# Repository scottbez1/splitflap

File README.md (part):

# Split-Flap Display

This is a DIY ESP32-based [split-flap display](https://en.wikipedia.org/wiki/Split-flap_display), optimized for easy assembly at home in small quantities but able to be scaled up to large affordable displays.

The [splitflap community Discord server](https://discord.com/invite/wgehm3PcrC) is the best place to keep up with the latest changes or ask questions about the project!

Want to help support development or just say "thanks"? Consider a one-time or monthly sponsorship:

| [:heart: Sponsor scottbez1 on GitHub](https://github.com/sponsors/scottbez1) |
|---|

**Using this project in a commercial setting or for paid client work?** Go right ahead - it's open source (just make sure to follow the terms of the Apache License)! I would, however, ask that you consider [sponsoring the project](https://github.com/sponsors/scottbez1). I've been developing and maintaining this project in my free time for over 10 years, and I'd love to continue working on it. Sponsorships allow me to pay for prototypes and development tools that make this project possible. Unlike pure software projects, every iteration has real hardware costs; sponsorships allow me to keep iterating and improving the project faster. Thank you!

# Current Status
[You can download the **latest stable releases** of the hardware designs from the official 'releases' page.](https://github.com/scottbez1/splitflap/releases)

Releases have been tested and used to produce working units, but as this is a continuously evolving open-source project, there may always be minor issues and/or incomplete documentation from time to time.

Here's a video of a large 108-module display powered by 18 Chainlink Driver boards and a Chainlink Base:

## Stable v2 Mechanical Release
As of 2025-01-19, the v2 refresh of the mechanical and sensor design is considered stable and recommended for new builds.

**Here's what's new in v2:**

- **52 flaps per module** for more character/symbol options
- **New printed flap design ("Epilogue")** with 52 flaps per set (see animation above), including several color-block flaps
- **Updated enclosure** and mechanical parts (laser-cut) to accomodate 52 flaps
  - Motor wires now exit downward for less awkward wiring!
- **New sensor PCB** that's easier to assemble and includes an LED for checking the magnet status
- **Software-configurable calibration** rather than mechanical sensor adjustment

**But many things are staying the same for easy upgrades/compatibility:**
- No change to flap dimensions!
- No changes to Chainlink Driver, Chainlink Buddy boards, or system architecture!
- 40-flap modules are still an officially supported option!
- Open source, as always!
- v0 parts (sensor kits) will continue to be stocked at Bezek Labs through mid-2025; don't worry if you haven't finished your build yet, the old sensor kits aren't going away for a little while!

I'd love to hear your thoughts and questions about this project, and happy to incorporate any feedback you might have into these designs! Please feel free (and encouraged) to [open GitHub issues](https://github.com/scottbez1/splitflap/issues/new), email me directly, reach out [on Bluesky](https://bsky.app/profile/scottbez1.bsky.social), and [get involved](https://github.com/scottbez1/splitflap/pulls) in the open source development and let's keep chatting and building together!

# Build Your Own
If you have any questions, please don't hesitate to ask in the [community Discord server](https://discord.gg/Hxnftc8PyW)!

* [**Documentation Index**](/docs/DocumentationIndex.md)
* [**Ordering guide (the "easy" route) v2**](/docs/v2/OrderingEasy.md)
* [**Comprehensive ordering guide**](/docs/v2/OrderingComplete.md)
* [**Chainlink Driver Electronics User Guide**](/docs/ElectronicsGuide.md)
* [**Assembly instructions v2**](/docs/v2/Assembly.md)
* [**Latest stable releases**](https://github.com/scottbez1/splitflap/releases)

# Table of Contents
- [Design Overview](#design-overview)
  - [Mechanical](#mechanical)
    - [Combined front panel (script)](#combined-front-panel-script)
    - [Flap font/sticker generator (script)](#flap-fontsticker-generator-script)
  - [Electronics](#electronics)
    - [Sensor PCBs](#sensor-pcbs-1-per-module)
    - [Chainlink Driver](#chainlink-driver-1-per-6-modules)
    - [Chainlink Buddy \[T-Display\]](#chainlink-buddy-t-display-1-for-entire-display)
    - [Advanced items](#advanced-items)
      - [Chainlink Buddy \[Breadboard\]](#chainlink-buddy-breadboard-1-for-entire-display-alternative-to-t-display)
      - [Chainlink Base](#chainlink-base-1-for-entire-display-large-displays)
    - [Older designs](#older-designs)
      - [Classic controller](#classic-controller-electronics-deprecated)
    + [Miscellaneous Tools](#miscellaneous-tools)
      - [3D Printed Tools](#3d-printed-tools)
      - [Chainlink Driver Tester](#chainlink-driver-tester)
  * [Code](#code)
    + [Firmware](#firmware)
    + [Computer Control Software](#computer-control-software)
- [Contributing/Modifying](#contributingmodifying)
  * [3D Design](#3d-design)
  * [Electronics Design](#electronics-design)

# Design Overview

## Mechanical
The mechanical/structural components are made from laser-cut 3mm MDF or acrylic, and held together with M4 bolts and nuts. The design is parametric and built using OpenSCAD. See below for more info on rendering/modifying the design.

You can view an interactive 3d model of the design [here](https://scottbez1.github.io/splitflap/embed.html?branch=master).

The v2 mechanical design officially supports variants with 52 flaps (perfect for use with the new ["Epilogue" printed flaps](https://bezeklabs.etsy.com/listing/1685633114/)) and 40 flaps. But you can always modify the design to customize it further.

### v2 (52-flap module option - recommended)

Instructions: [v2 assembly guide](/docs/v2/Assembly.md)

Module dimensions: 

Latest auto-generated (untested!) artifacts<sup>:warning:</sup>:
* For Ponoko 3mm MDF ([svg](https://s3.amazonaws.com/splitflap-artifacts/master/3d/3d_laser_vector-52-ponoko-3mm-mdf_1x.svg)) 
* For Ponoko 3mm acrylic ([svg](https://s3.amazonaws.com/splitflap-artifacts/master/3d/3d_laser_vector-52-ponoko-3mm-acrylic_1x.svg)) 
* For generic material (0.18mm kerf correction) ([svg](https://s3.amazonaws.com/splitflap-artifacts/master/3d/3d_laser_vector-52.svg))
* For Elecrow 3mm Wood ([zipped pdf](https://s3.amazonaws.com/splitflap-artifacts/master/3d/3d_laser_vector-52-elecrow-3mm-wood_1x.zip))
* For Elecrow 3mm Acrylic ([zipped pdf](https://s3.amazonaws.com/splitflap-artifacts/master/3d/3d_laser_vector-52-elecrow-3mm-acrylic_1x.zip))

<sup>:warning:</sup>For tested/stable/recommended artifacts, always use the [latest release](https://github.com/scottbez1/splitflap/releases) instead, as the links on this page will change over time.

### v2 (40-flap module option)

Instructions: [v2 assembly guide](/docs/v2/Assembly.md)

Module dimensions: 

Latest auto-generated (untested!) artifacts<sup>:warning:</sup>:
* For Ponoko 3mm MDF ([svg](https://s3.amazonaws.com/splitflap-artifacts/master/3d/3d_laser_vector-40-ponoko-3mm-mdf_1x.svg)) 
* For Ponoko 3mm acrylic ([svg](https://s3.amazonaws.com/splitflap-artifacts/master/3d/3d_laser_vector-40-ponoko-3mm-acrylic_1x.svg)) 
* For generic material (0.18mm kerf correction) ([svg](https://s3.amazonaws.com/splitflap-artifacts/master/3d/3d_laser_vector-52.svg))
* For Elecrow 3mm Wood ([zipped pdf](https://s3.amazonaws.com/splitflap-artifacts/master/3d/3d_laser_vector-40-elecrow-3mm-wood_1x.zip))
* For Elecrow 3mm Acrylic ([zipped pdf](https://s3.amazonaws.com/splitflap-artifacts/master/3d/3d_laser_vector-40-elecrow-3mm-acrylic_1x.zip))

<sup>:warning:</sup>For tested/stable/recommended artifacts, always use the [latest release](https://github.com/scottbez1/splitflap/releases) instead, as the links on this page will change over time.

### Combined front panel (script)
By default, the design will have a separate laser-cut faceplate for each individual module. For larger displays you may want to combine front panels into a single piece, and the repo has a script to help with this.

You can modify:
* Number of rows and columns
* Horizontal and vertical spacing/separation of modules
* Overall outer width and height of the panel

There are a lot of options; see the `--help` for explanations.

#### Example 1 - Laser cut 6x1

```
python3 3d/scripts/generate_combined_front_panel.py \
  --kerf-preset elecrow-3mm-acrylic \
  --num-flaps 52 \
  --cols 6 \
  --rows 1 \
  --spacing-x 0 \
  --spacing-y 0 \
  --frame-margin-x 0 \
  --frame-margin-y 0 \
  --center-mode module
```

#### Example 2 - CNC router 12x2, with frame margin

For CNC cutting, the script supports rendering a vector file optimized for thicker material (e.g. 6mm MDF) where only the bolt-holes will be through-cut. In this mode, the slots for the top/bottom enclosure pieces can be cut as ~4mm pockets so they aren't visible from the front face. The script automatically generates dog-bone shapes for these pocket cuts.

This example also demonstrates use of the --frame-margin-x and --frame-margin-y options to add an additional margin of 20mm horizontally and 4mm vertically to the front panel dimensions.

```
python3 3d/scripts/generate_combined_front_panel.py \
  --tool-diameter 3.175 \
  --num-flaps 52 \
  --cols 12 \
  --rows 2 \
  --spacing-x 0 \
  --spacing-y 0 \
  --frame-margin-x 20 \
  --frame-margin-y 4 \
  --center-mode module
```

### Flap font/sticker generator (script)
If you'd like to print your own flaps, or cut custom vinyl letter stickers, the project includes a script (`generate_fonts.py`) to generate vector design files, which is extremely configurable:

* Font for text
  * This is further customizable in `flap_fonts.scad` -- this is where font parameters are defined like the overall font scale, position offsets, and even per-character scale and position overrides in case you need to tweak particularly problematic letters (e.g. a really wide "W" or an "@" with too thin of a stroke).
* Character-set - which letters/numbers/symbols/colors are included and in what order
* Bleed - extends rendering past the borders of the flaps to compensate for slight misalignment of printing and cutting operations
* Keepout areas - option to highlight keepout violations for manual review, automatically clip them, or ignore them
* Rendering options:
    * Single-sided - useful for previewing how all letters will look on flaps
    * Front/back - for batch duplex printing, generate separate front-side and back-side files (e.g. sign shop printing on a flat sheet of PVC)
    * Side-by-side - for individual flap printing, each flap's front design is laid out side-by-side with its back design

There are a lot of options; see the `--help` for explanations.

#### Example 1 - Epilogue font, rendered in front+back pairs, default character set, 1mm bleed (for printing)

```
python3 3d/scripts/generate_fonts.py \
  --mode side-by-side \
  --font Epilogue \
  --columns 4 \
  --bleed 1 \
  --fill
```

## Electronics
> [!NOTE]
> For small displays (up to 3 modules), you can skip the custom controller boards and use off-the-shelf ULN2003A driver
modules plugged into an Arduino Uno. This is [partially documented in the wiki](https://github.com/scottbez1/splitflap/wiki/Electronics#basic-prototyping-alternative-electronics-approach)
> but may require some additional tinkering to get it to work. _Help wanted: if you'd like to help improve these instructions,
> please reach out in the Discord server, thanks!_

The "Chainlink" electronics system is designed to support long chains of driver boards to control medium/large displays (up to 100+ split-flap modules).
It's also designed to be easy and cheap to order pre-assembled or build yourself, especially in higher
quantities, due to its simple BOM and surface-mount components.

To build a display, you'll need 3 different electronics:
* One **Sensor PCB** for every split-flap module
* One **Chainlink Driver** board for every 6 split-flap modules. This is what interfaces with the motors and sensors of each module. Chainlink Driver boards can be chained together to construct a large display.
* An ESP32 microcontroller board. There are a few options:
    * For small/medium displays, one of the **Chainlink Buddy** boards are recommended
        * **Chainlink Buddy [T-Display]**  holds a Lilygo T-Display ESP32 module which includes a built-in LCD and 2 buttons
        * **Chainlink Buddy [Breadboard]** makes it easy to connect a Chainlink Driver to a breadboard for prototyping, though you can also easily connect a Chainlink Driver to a breadboard with a few dupont wires.
    * For large displays, the **Chainlink Base** provides a number of advanced features: central
power management/distribution and fault monitoring, UART and RS-485 connections, configuration switches, and status LEDs.

### Sensor PCBs (1 per module)
Each module needs a hall-effect sensor for start-up calibration and fault monitoring. 

#### Sensors v2

New sensors for the v2 laser-cut hardware - these use surface mount components and are optimized for PCB assembly at JLCPCB. These new sensors are not compatible with v0.7 and older laser-cut hardware.

Packs of 6 sensors are [available mostly-assembled in the Bezek Labs store](https://bezeklabs.etsy.com/listing/1696745674),
and come with the right-angle pin headers and magnets you'll need. Purchases support continued development of this project.

Latest auto-generated (untested!) artifacts<sup>:warning:</sup>:

* Schematic [pdf](https://s3.amazonaws.com/splitflap-artifacts/master/electronics-v2/sensor_smd-schematic.pdf)
* Interactive BOM (for manual assembly) [interactive](https://s3.amazonaws.com/splitflap-artifacts/master/electronics-v2/sensor_smd-ibom.html)
* Fabrication files (single)
  * NOTE: PCBs must be 0.8mm! (rather than the more typical 1.6mm thickness)
  * PCB gerbers [zip](https://s3.amazonaws.com/splitflap-artifacts/master/electronics-v2/sensor_smd-jlc/gerbers.zip)
  * PCB BOM (for JLCPCB assembly) [csv](https://s3.amazonaws.com/splitflap-artifacts/master/electronics-v2/sensor_smd-jlc/bom.csv)
  * PCB CPL (for JLCPCB assembly) [csv](https://s3.amazonaws.com/splitflap-artifacts/master/electronics-v2/sensor_smd-jlc/pos.csv)
* Fabrication files (panelized)
  * NOTE: PCBs must be 0.8mm! (rather than the more typical 1.6mm thickness)
  * PCB gerbers [zip](https://s3.amazonaws.com/splitflap-artifacts/master/electronics-v2/sensor_smd-panelized-jlc/gerbers.zip)
  * PCB BOM (for JLCPCB assembly) [csv](https://s3.amazonaws.com/splitflap-artifacts/master/electronics-v2/sensor_smd-panelized-jlc/bom.csv)
  * PCB CPL (for JLCPCB assembly) [csv](https://s3.amazonaws.com/splitflap-artifacts/master/electronics-v2/sensor_smd-panelized-jlc/pos.csv)
* Purchase sensor kits in the US: [Bezek Labs](https://bezeklabs.etsy.com/listing/1696745674)

<sup>:warning:</sup>For tested/stable/recommended artifacts, always use the [latest release](https://github.com/scottbez1/splitflap/releases) instead, as the links on this page will change over time.

### Chainlink Driver (1 per 6 modules)

Key features:
* Controls 6 split-flap modules per board
* Primarily SMD and all components (except the pin headers and motor connectors) are available in JLCPCB's parts library
for easy SMD/THT assembly
* Clock and latch lines are buffered on each board with a 74HC125 to support longer chains
* 2 bits of loopback error checking per board (connecting 2 spare output bits on output shift registers to 2 spare inputs) allows the controller
to validate data integrity up and down the whole chain
* Module order goes from right-to-left since this is intended to be installed and accessed from *behind* the modules

Chainlink Driver boards are [available mostly-assembled in the Bezek Labs store](https://bezeklabs.etsy.com/listing/1123280069/splitflap-chainlink-driver-v11),
and come with the additional connectors and ribbon cables you'll need. Purchases support continued development of this project.

More information on building and using Chainlink Drivers is available in the [Chainlink Driver User Guide](/docs/ElectronicsGuide.md).

Or if you'd like to order these directly from a fab, this design is optimized for assembly at JLCPCB, and files are automatically generated
for ordering *assembled* PCBs there. Or if you wish to assemble this board yourself instead of paying for assembly, 
you can view the [interactive BOM/placement tool](https://s3.amazonaws.com/splitflap-artifacts/master/electronics-chainlink/bom/chainlinkDriver-ibom.html)

Depending on available stock at JLCPCB, you may need to manually modify the BOM file to use alternative components, or regenerate the files
yourself using `export_jlcpcb.py` and specifying one or more `LCSC_ALT_*` field names to use a pre-selected alternative part number. See
the schematic for available pre-selected alternatives (check the symbol's properties/fields).

Latest auto-generated (untested!) artifacts<sup>:warning:</sup>:

* Schematic [pdf](https://s3.amazonaws.com/splitflap-artifacts/master/electronics-chainlink/chainlinkDriver-schematic.pdf)
* PCB overview [pdf](https://s3.amazonaws.com/splitflap-artifacts/master/electronics-chainlink/chainlinkDriver-pcb-packet.pdf)
* PCB gerbers [zip](https://s3.amazonaws.com/splitflap-artifacts/master/electronics-chainlink/chainlinkDriver-jlc/gerbers.zip)
* PCB bom (for JLCPCB assembly) [csv](https://s3.amazonaws.com/splitflap-artifacts/master/electronics-chainlink/chainlinkDriver-jlc/bom.csv)
* PCB CPL (for JLCPCB assembly) [csv](https://s3.amazonaws.com/splitflap-artifacts/master/electronics-chainlink/chainlinkDriver-jlc/pos.csv)
* PCB bom (for manual assembly) [interactive](https://s3.amazonaws.com/splitflap-artifacts/master/electronics-chainlink/bom/chainlinkDriver-ibom.html)

<sup>:warning:</sup>For tested/stable/recommended artifacts, always use the [latest release](https://github.com/scottbez1/splitflap/releases) instead, as the links on this page will change over time.

### Chainlink Buddy \[T-Display\] (1 for entire display)

The Chainlink Buddy \[T-Display\] is a convenient way to connect a T-Display ESP32 board (recommended microcontroller) to a chain
of Chainlink Drivers.

Key features:
* TTGO T-Display ESP32 module as the controller, which includes USB-C, color IPS LCD display and buttons
* Extra terminals for every pin of the T-Display allow you to connect any other peripherals to the ESP32 (the connection to the Chainlink Driver requires _only 4_ of the GPIOs)
* Optional barrel jack makes it easy to use a "wall wart" AC adapter/power-supply (since the Chainlink Driver only has screw terminals for power) -- plug in a 12V supply
and then run a wire from the onboard screw terminals to the Chainlink Driver's motor power screw terminals.
* Optional 5V regulator allows for powering the ESP32 without a USB connection, using the 12V motor power supply

Chainlink Buddy \[T-Display\] boards are [available in the Bezek Labs store](https://bezeklabs.etsy.com/listing/1109357786/splitflap-chainlink-buddy-t-display),
and come with the additional connectors you'll need. Purchases support continued development of this project. 

Latest auto-generated (untested!) artifacts<sup>:warning:</sup>:

* Schematic [pdf](https://s3.amazonaws.com/splitflap-artifacts/master/electronics-chainlink-buddy-t-display/chainlinkBuddyTDisplay-schematic.pdf)
* PCB ([gerbers](https://s3.amazonaws.com/splitflap-artifacts/master/electronics-chainlink-buddy-t-display/chainlinkBuddyTDisplay-jlc/gerbers.zip) / [pdf](https://s3.amazonaws.com/splitflap-artifacts/master/electronics-chainlink-buddy-t-display/chainlinkBuddyTDisplay-pcb-packet.pdf))
* Panelized PCB ([gerbers](https://s3.amazonaws.com/splitflap-artifacts/master/electronics-chainlink-buddy-t-display/chainlinkBuddyTDisplay-panelized-jlc/gerbers.zip) / [pdf](https://s3.amazonaws.com/splitflap-artifacts/master/electronics-chainlink-buddy-t-display/chainlinkBuddyTDisplay-panelized-pcb-packet.pdf))
* PCB bom (for manual assembly) [interactive](https://s3.amazonaws.com/splitflap-artifacts/master/electronics-chainlink-buddy-t-display/bom/chainlinkBuddyTDisplay-ibom.html)

<sup>:warning:</sup>For tested/stable/recommended artifacts, always use the [latest release](https://github.com/scottbez1/splitflap/releases) instead, as the links on this page will change over time.

### Advanced items
#### Chainlink Buddy \[Breadboard\] (1 for entire display; alternative to T-Display)

The Chainlink Buddy \[Breadboard\] makes it easy to connect a Chainlink Driver to a breadboard for prototyping. You could use 5 dupont wires and have a
messy rats nest, or you could use a single ribbon cable and this slick breakout board.

Chainlink Buddy \[Breadboard\] boards are [available in the Bezek Labs store](https://bezeklabs.etsy.com/listing/1123863267/splitflap-chainlink-buddy-breadboard),
and come with the additional connectors you'll need. Purchases support continued development of this project. 

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
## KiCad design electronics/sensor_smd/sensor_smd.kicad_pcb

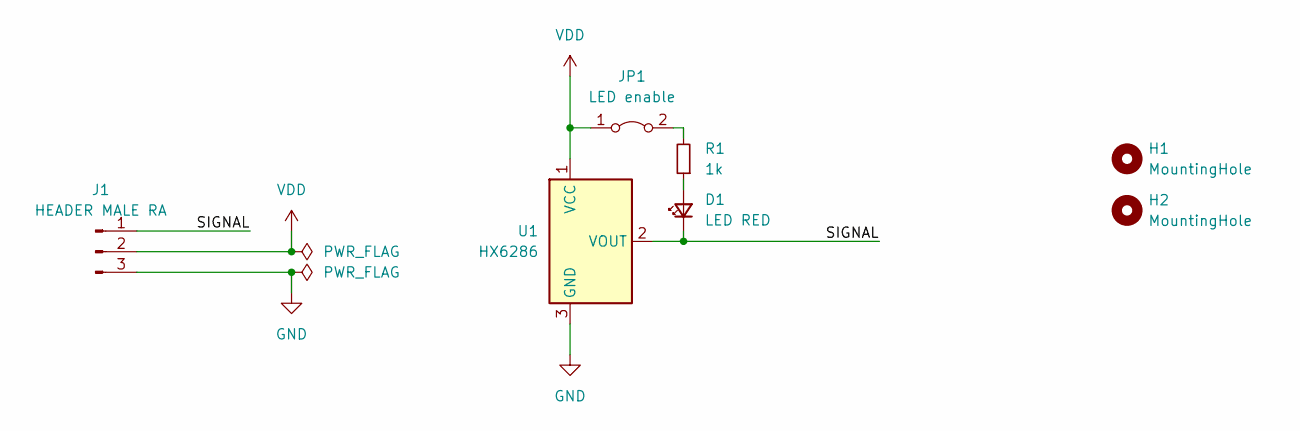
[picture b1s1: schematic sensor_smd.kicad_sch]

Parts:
D1: LED RED; LED_0603_1608Metric; LCSC C2286
H1: MountingHole; MountingHole_4.3mm_M4_ISO7380
H2: MountingHole; hole_9.4
J1: HEADER MALE RA; header_3_smd
JP1: LED enable; SolderJumper-2_P1.3mm_Bridged_Pad1.0x1.5mm
R1: 1k; R_0603_1608Metric; LCSC C21190
U1: HX6286; SOT-23W; LCSC C495736

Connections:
/SIGNAL: D1.1 (K), J1.1, U1.2 (VOUT)
GND: J1.3, U1.3 (GND)
unnamed: D1.2 (A), R1.1
unnamed: JP1.2 (B), R1.2
VDD: J1.2, JP1.1 (A), U1.1 (VCC)

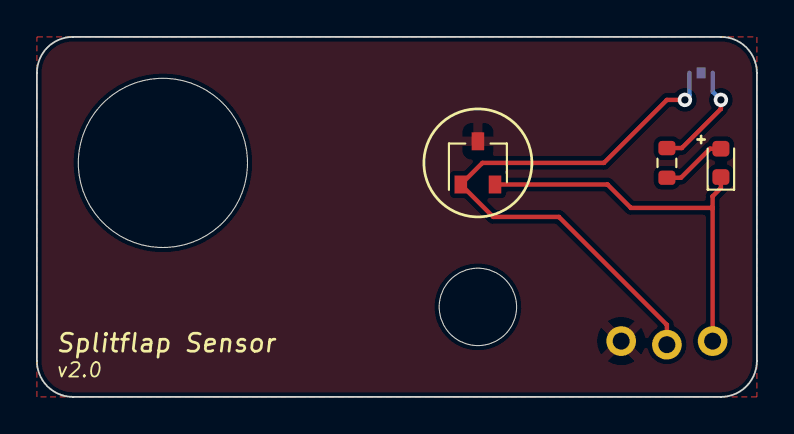
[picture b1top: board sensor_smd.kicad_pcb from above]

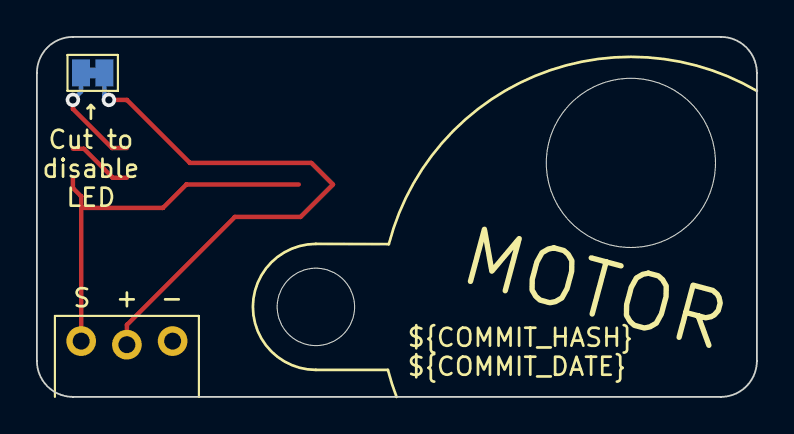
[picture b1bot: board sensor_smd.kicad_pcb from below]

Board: 2 copper layers, 40.0 x 20.0 mm, 7 parts (2 on the bottom side), 5 nets.

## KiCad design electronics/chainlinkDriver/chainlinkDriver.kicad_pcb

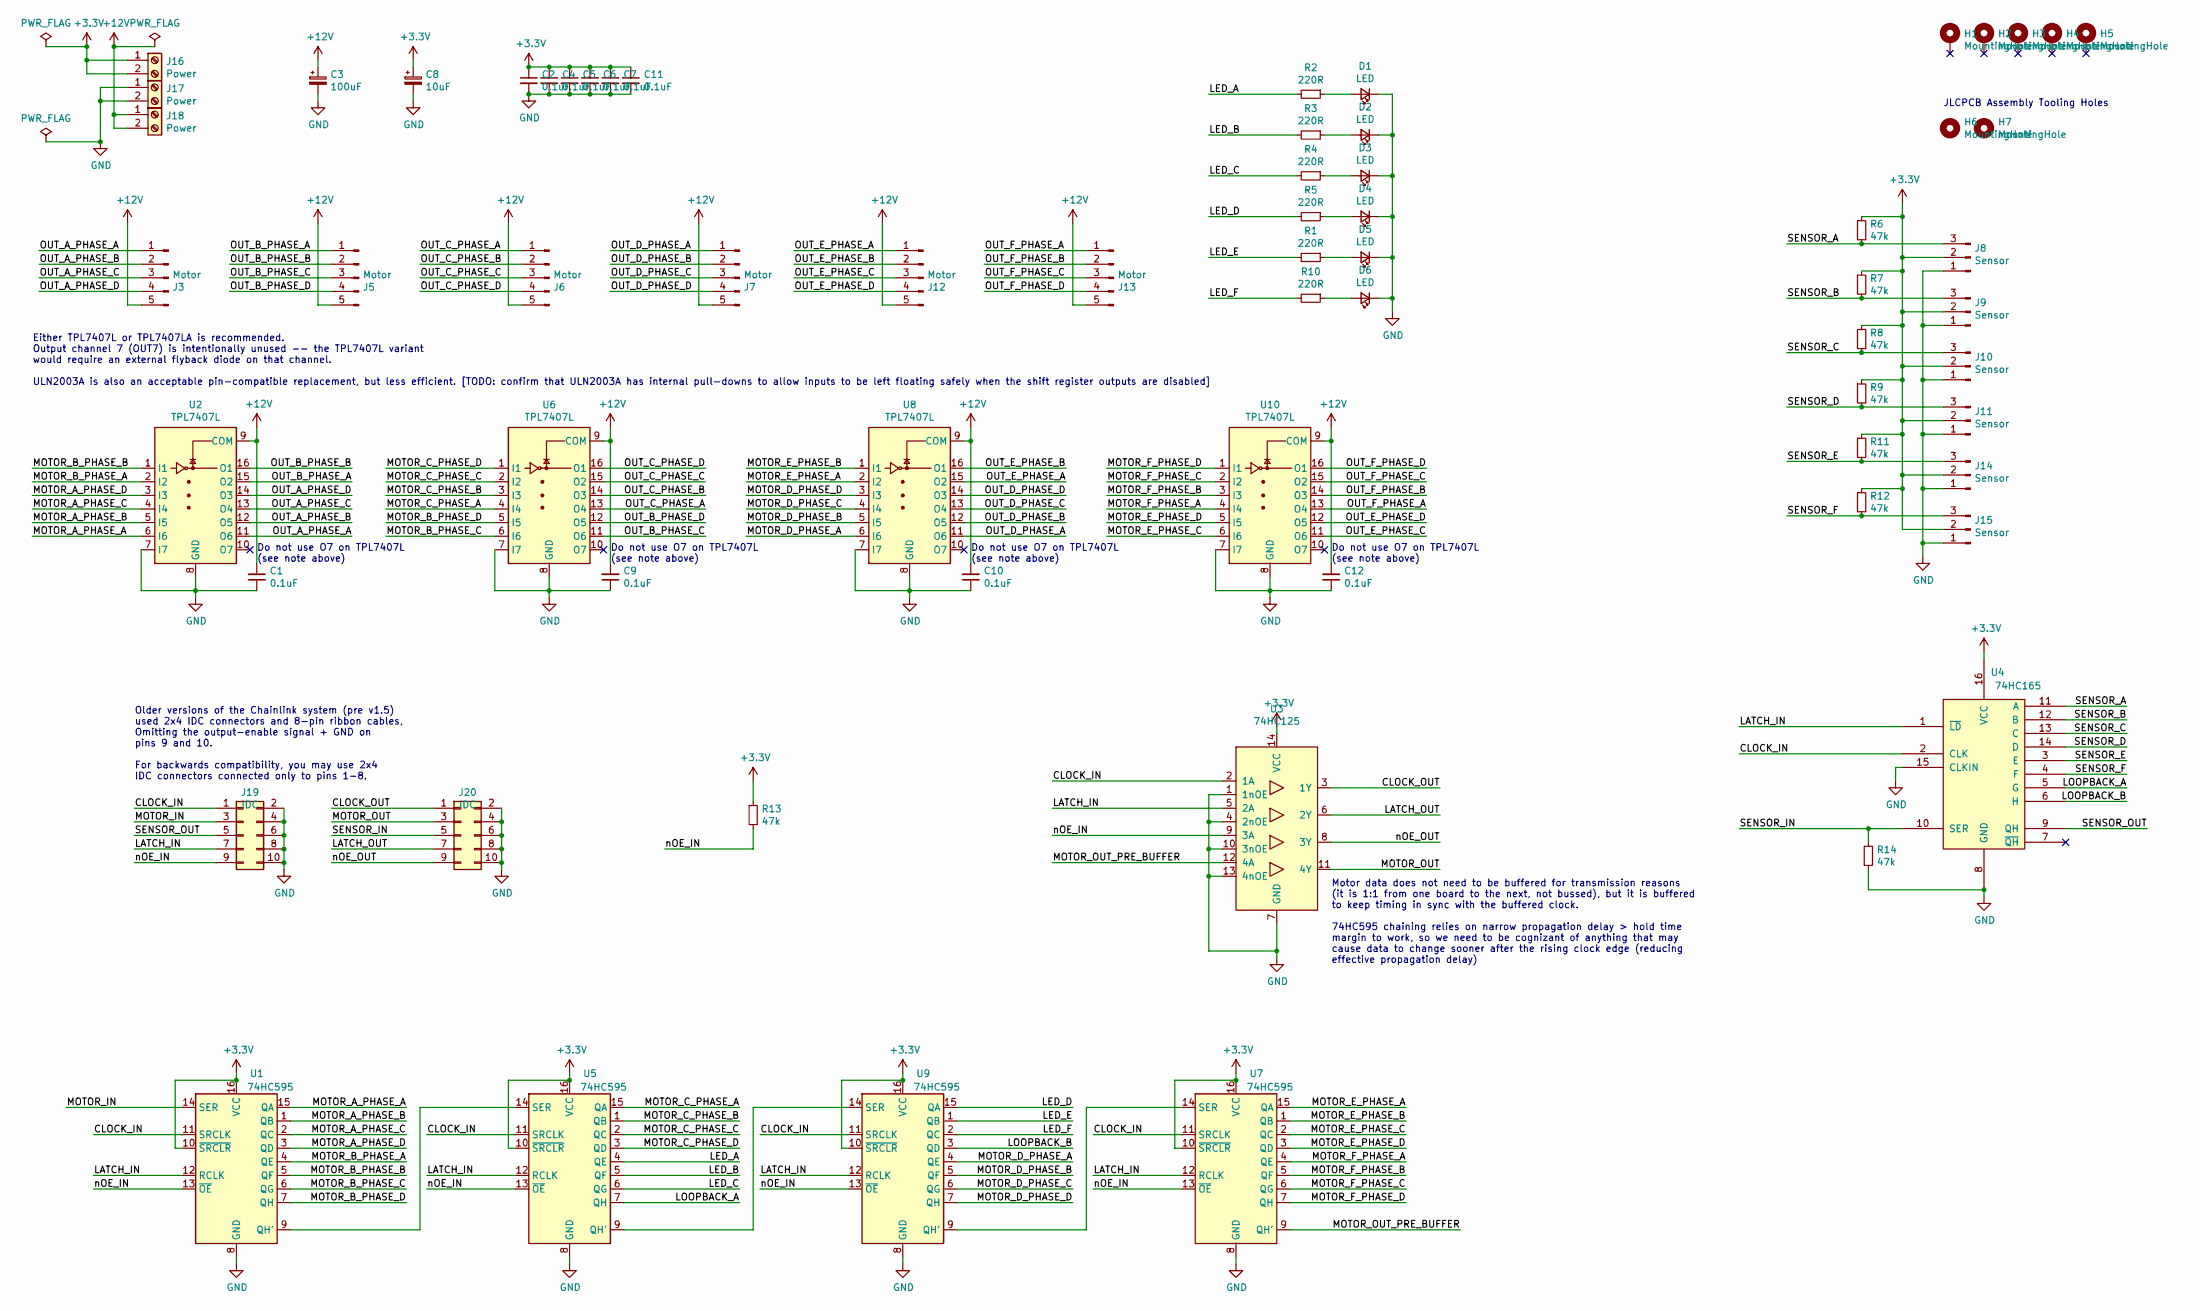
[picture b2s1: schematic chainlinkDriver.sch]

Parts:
C1, C2, C4, C5, C6, C7, C9, C10, C11, C12: 0.1uF; C_0603_1608Metric; LCSC C14663
C3: 100uF; CP_Elec_8x10; LCSC C176665
C8: 10uF; CP_Elec_4x5.3; LCSC C134721
D1, D2, D3, D4, D5, D6: LED; LED_0603_1608Metric_Silkscreen; LCSC C2286
H1, H2, H3, H4, H5: MountingHole; MountingHole_3.2mm_M3_ISO7380_Pad
H6, H7: MountingHole; AssemblyToolingHole
J3, J5, J6, J7, J12, J13: Motor; JST_XH_B5B-XH-A_1x05_P2.50mm_Vertical
J8, J9, J10, J11, J14, J15: Sensor; PinHeader_1x03_P2.54mm_Vertical_Locking
J16, J17, J18: Power; Generic-5.08-2P; LCSC C8465
J19, J20: IDC; IDC-Header_2x05_P2.54mm_Vertical_2x04Silk
R1, R2, R3, R4, R5, R10: 220R; R_0603_1608Metric; LCSC C22962
R6, R7, R8, R9, R11, R12, R13, R14: 47k; R_0603_1608Metric; LCSC C25819
U1, U5, U7, U9: 74HC595; SOIC-16_3.9x9.9mm_P1.27mm_silk; LCSC C5947
U2, U6, U8, U10: TPL7407L; SOIC-16_3.9x9.9mm_P1.27mm_silk; LCSC C139663
U3: 74HC125; SOIC-14_3.9x8.7mm_P1.27mm_silk; LCSC C5598
U4: 74HC165; SOIC-16_3.9x9.9mm_P1.27mm_silk; LCSC C5613

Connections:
+3V3: C2.1, C4.1, C5.1, C6.1, C7.1, C8.1, C11.1, J8.2, J9.2, J10.2, J11.2, J14.2, J15.2, J16.1, J16.2, R6.1, R7.1, R8.1, R9.1, R11.1, R12.1, R13.1, U1.10 (~SRCLR), U1.16 (VCC), U3.14 (VCC), U4.16 (VCC), U5.10 (~SRCLR), U5.16 (VCC), U7.10 (~SRCLR), U7.16 (VCC), U9.10 (~SRCLR), U9.16 (VCC)
+12V: C1.2, C3.1, C9.2, C10.2, C12.2, J3.5, J5.5, J6.5, J7.5, J12.5, J13.5, J18.1, J18.2, U2.9 (COM), U6.9 (COM), U8.9 (COM), U10.9 (COM)
/CLOCK_IN: J19.1, U1.11 (SRCLK), U3.2 (1A), U4.2 (CLK), U5.11 (SRCLK), U7.11 (SRCLK), U9.11 (SRCLK)
/CLOCK_OUT: J20.1, U3.3 (1Y)
/LATCH_IN: J19.7, U1.12 (RCLK), U3.5 (2A), U4.1 (~LD), U5.12 (RCLK), U7.12 (RCLK), U9.12 (RCLK)
/LATCH_OUT: J20.7, U3.6 (2Y)
/LED_A: R2.2, U5.4 (QE)
/LED_B: R3.2, U5.5 (QF)
/LED_C: R4.2, U5.6 (QG)
/LED_D: R5.2, U9.15 (QA)
/LED_E: R1.2, U9.1 (QB)
/LED_F: R10.2, U9.2 (QC)
/LOOPBACK_A: U4.5 (G), U5.7 (QH)
/LOOPBACK_B: U4.6 (H), U9.3 (QD)
/MOTOR_A_PHASE_A: U1.15 (QA), U2.6 (I6)
/MOTOR_A_PHASE_B: U1.1 (QB), U2.5 (I5)
/MOTOR_A_PHASE_C: U1.2 (QC), U2.4 (I4)
/MOTOR_A_PHASE_D: U1.3 (QD), U2.3 (I3)
/MOTOR_B_PHASE_A: U1.4 (QE), U2.2 (I2)
/MOTOR_B_PHASE_B: U1.5 (QF), U2.1 (I1)
/MOTOR_B_PHASE_C: U1.6 (QG), U6.6 (I6)
/MOTOR_B_PHASE_D: U1.7 (QH), U6.5 (I5)
/MOTOR_C_PHASE_A: U5.15 (QA), U6.4 (I4)
/MOTOR_C_PHASE_B: U5.1 (QB), U6.3 (I3)
/MOTOR_C_PHASE_C: U5.2 (QC), U6.2 (I2)
/MOTOR_C_PHASE_D: U5.3 (QD), U6.1 (I1)
/MOTOR_D_PHASE_A: U8.6 (I6), U9.4 (QE)
/MOTOR_D_PHASE_B: U8.5 (I5), U9.5 (QF)
/MOTOR_D_PHASE_C: U8.4 (I4), U9.6 (QG)
/MOTOR_D_PHASE_D: U8.3 (I3), U9.7 (QH)
/MOTOR_E_PHASE_A: U7.15 (QA), U8.2 (I2)
/MOTOR_E_PHASE_B: U7.1 (QB), U8.1 (I1)
/MOTOR_E_PHASE_C: U7.2 (QC), U10.6 (I6)
/MOTOR_E_PHASE_D: U7.3 (QD), U10.5 (I5)
/MOTOR_F_PHASE_A: U7.4 (QE), U10.4 (I4)
/MOTOR_F_PHASE_B: U7.5 (QF), U10.3 (I3)
/MOTOR_F_PHASE_C: U7.6 (QG), U10.2 (I2)
/MOTOR_F_PHASE_D: U7.7 (QH), U10.1 (I1)
/MOTOR_IN: J19.3, U1.14 (SER)
/MOTOR_OUT: J20.3, U3.11 (4Y)
/MOTOR_OUT_PRE_BUFFER: U3.12 (4A), U7.9 (QH')
/OUT_A_PHASE_A: J3.1, U2.11 (O6)
/OUT_A_PHASE_B: J3.2, U2.12 (O5)
/OUT_A_PHASE_C: J3.3, U2.13 (O4)
/OUT_A_PHASE_D: J3.4, U2.14 (O3)
/OUT_B_PHASE_A: J5.1, U2.15 (O2)
/OUT_B_PHASE_B: J5.2, U2.16 (O1)
/OUT_B_PHASE_C: J5.3, U6.11 (O6)
/OUT_B_PHASE_D: J5.4, U6.12 (O5)
/OUT_C_PHASE_A: J6.1, U6.13 (O4)
/OUT_C_PHASE_B: J6.2, U6.14 (O3)
/OUT_C_PHASE_C: J6.3, U6.15 (O2)
/OUT_C_PHASE_D: J6.4, U6.16 (O1)
/OUT_D_PHASE_A: J7.1, U8.11 (O6)
/OUT_D_PHASE_B: J7.2, U8.12 (O5)
/OUT_D_PHASE_C: J7.3, U8.13 (O4)
/OUT_D_PHASE_D: J7.4, U8.14 (O3)
/OUT_E_PHASE_A: J12.1, U8.15 (O2)
/OUT_E_PHASE_B: J12.2, U8.16 (O1)
/OUT_E_PHASE_C: J12.3, U10.11 (O6)
/OUT_E_PHASE_D: J12.4, U10.12 (O5)
/OUT_F_PHASE_A: J13.1, U10.13 (O4)
/OUT_F_PHASE_B: J13.2, U10.14 (O3)
/OUT_F_PHASE_C: J13.3, U10.15 (O2)
/OUT_F_PHASE_D: J13.4, U10.16 (O1)
/SENSOR_A: J8.3, R6.2, U4.11 (A)
/SENSOR_B: J9.3, R7.2, U4.12 (B)
/SENSOR_C: J10.3, R8.2, U4.13 (C)
/SENSOR_D: J11.3, R9.2, U4.14 (D)
/SENSOR_E: J14.3, R11.2, U4.3 (E)
/SENSOR_F: J15.3, R12.2, U4.4 (F)
/SENSOR_IN: J20.5, R14.1, U4.10 (SER)
/SENSOR_OUT: J19.5, U4.9 (QH)
/nOE_IN: J19.9, R13.2, U1.13 (~OE), U3.9 (3A), U5.13 (~OE), U7.13 (~OE), U9.13 (~OE)
/nOE_OUT: J20.9, U3.8 (3Y)
GND: C1.1, C2.2, C3.2, C4.2, C5.2, C6.2, C7.2, C8.2, C9.1, C10.1, C11.2, C12.1, D1.1 (K), D2.1 (K), D3.1 (K), D4.1 (K), D5.1 (K), D6.1 (K), J8.1, J9.1, J10.1, J11.1, J14.1, J15.1, J17.1, J17.2, J19.2, J19.4, J19.6, J19.8, J19.10, J20.2, J20.4, J20.6, J20.8, J20.10, R14.2, U1.8 (GND), U2.7 (I7), U2.8 (GND), U3.1 (1nOE), U3.4 (2nOE), U3.7 (GND), U3.10 (3nOE), U3.13 (4nOE), U4.8 (GND), U4.15 (CLKIN), U5.8 (GND), U6.7 (I7), U6.8 (GND), U7.8 (GND), U8.7 (I7), U8.8 (GND), U9.8 (GND), U10.7 (I7), U10.8 (GND)
unnamed: D1.2 (A), R2.1
unnamed: D2.2 (A), R3.1
unnamed: D3.2 (A), R4.1
unnamed: D4.2 (A), R5.1
unnamed: D5.2 (A), R1.1
unnamed: D6.2 (A), R10.1
unnamed: U1.9 (QH'), U5.14 (SER)
unnamed: U5.9 (QH'), U9.14 (SER)
unnamed: U7.14 (SER), U9.9 (QH')

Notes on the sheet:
JLCPCB Assembly Tooling Holes
Either TPL7407L or TPL7407LA is recommended. Output channel 7 (OUT7) is intentionally unused -- the TPL7407L variant would require an external flyback diode on that channel. ULN2003A is also an acceptable pin-compatible replacement, but less efficient. [TODO: confirm that ULN2003A has internal pull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
Do not use O7 on TPL7407L (see note above)
Motor data does not need to be buffered for transmission reasons (it is 1:1 from one board to the next, not bussed), but it is buffered to keep timing in sync with the buffered clock. 74HC595 chaining relies on narrow propagation delay > hold time margin to work, so we need to be cognizant of anyth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
Older versions of the Chainlink system (pre v1.5) used 2x4 IDC connectors and 8-pin ribbon cables, Omitting the output-enable signal + GND on pins 9 and 10. For backwards compatibility, you may use 2x4 IDC connectors connected only to pins 1-8.

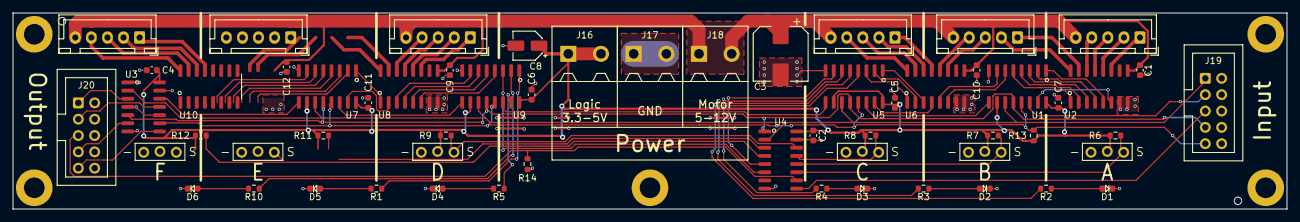
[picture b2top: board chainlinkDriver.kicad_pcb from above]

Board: 2 copper layers, 198.1 x 30.5 mm, 66 parts (0 on the bottom side), 85 nets.

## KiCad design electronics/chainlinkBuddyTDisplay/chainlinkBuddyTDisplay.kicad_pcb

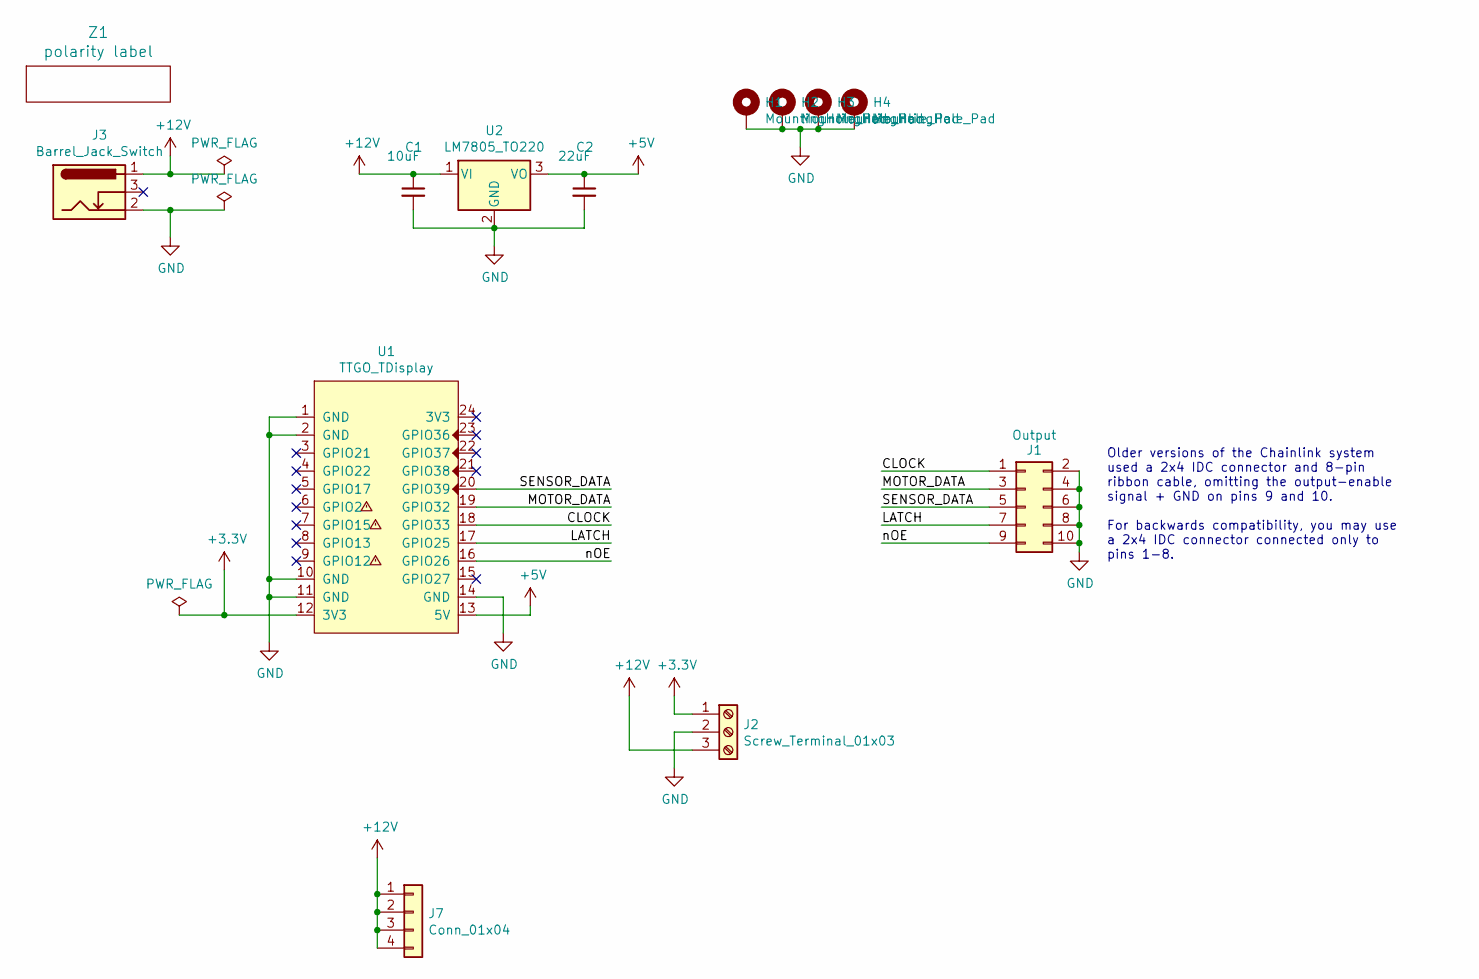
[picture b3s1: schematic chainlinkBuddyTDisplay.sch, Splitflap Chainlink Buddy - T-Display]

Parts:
C1: 10uF; C_1206_3216Metric_Pad1.33x1.80mm_HandSolder
C2: 22uF; C_1206_3216Metric_Pad1.33x1.80mm_HandSolder
H1, H2, H3, H4: MountingHole_Pad; MountingHole_3.2mm_M3_ISO7380_Pad
J1: Output; IDC-Header_2x05_P2.54mm_Vertical_2x04Silk
J2: Screw_Terminal_01x03; Generic-5.08-3P
J3: Barrel_Jack_Switch; PJ-202A
J7: Conn_01x04; PinHoles_1x04_P2.54mm_NoSilk
U1: TTGO_TDisplay; T-DISPLAY_extra_pins_labeled_double
U2: LM7805_TO220; TO-220-3_Vertical
Z1: polarity label; Symbol_Barrel_Polarity

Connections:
+3V3: J2.1, U1.12 (3V3)
+5V: C2.1, U1.13 (5V), U2.3 (VO)
+12V: C1.1, J2.3, J3.1, J7.1, J7.2, J7.3, J7.4, U2.1 (VI)
/CLOCK: J1.1, U1.18 (GPIO33)
/LATCH: J1.7, U1.17 (GPIO25)
/MOTOR_DATA: J1.3, U1.19 (GPIO32)
/SENSOR_DATA: J1.5, U1.20 (GPIO39)
/nOE: J1.9, U1.16 (GPIO26)
GND: C1.2, C2.2, H1.1, H2.1, H3.1, H4.1, J1.2, J1.4, J1.6, J1.8, J1.10, J2.2, J3.2, U1.1 (GND), U1.2 (GND), U1.10 (GND), U1.11 (GND), U1.14 (GND), U2.2 (GND)

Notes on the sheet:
Older versions of the Chainlink system used a 2x4 IDC connector and 8-pin ribbon cable, omitting the output-enable signal + GND on pins 9 and 10. For backwards compatibility, you may use a 2x4 IDC connector connected only to pins 1-8.

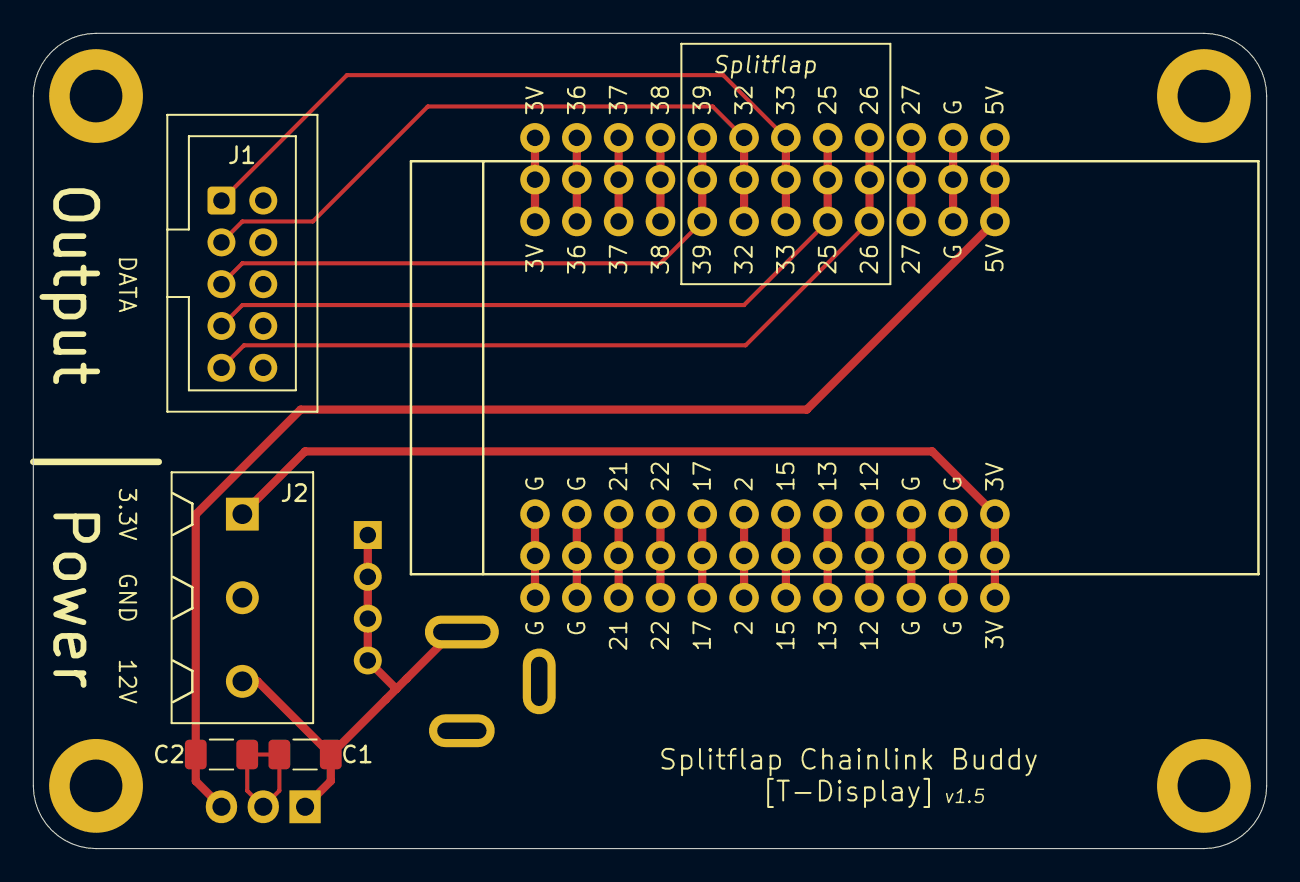
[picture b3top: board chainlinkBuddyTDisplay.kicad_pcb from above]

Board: 2 copper layers, 74.9 x 49.5 mm, 13 parts (1 on the bottom side), 9 nets.

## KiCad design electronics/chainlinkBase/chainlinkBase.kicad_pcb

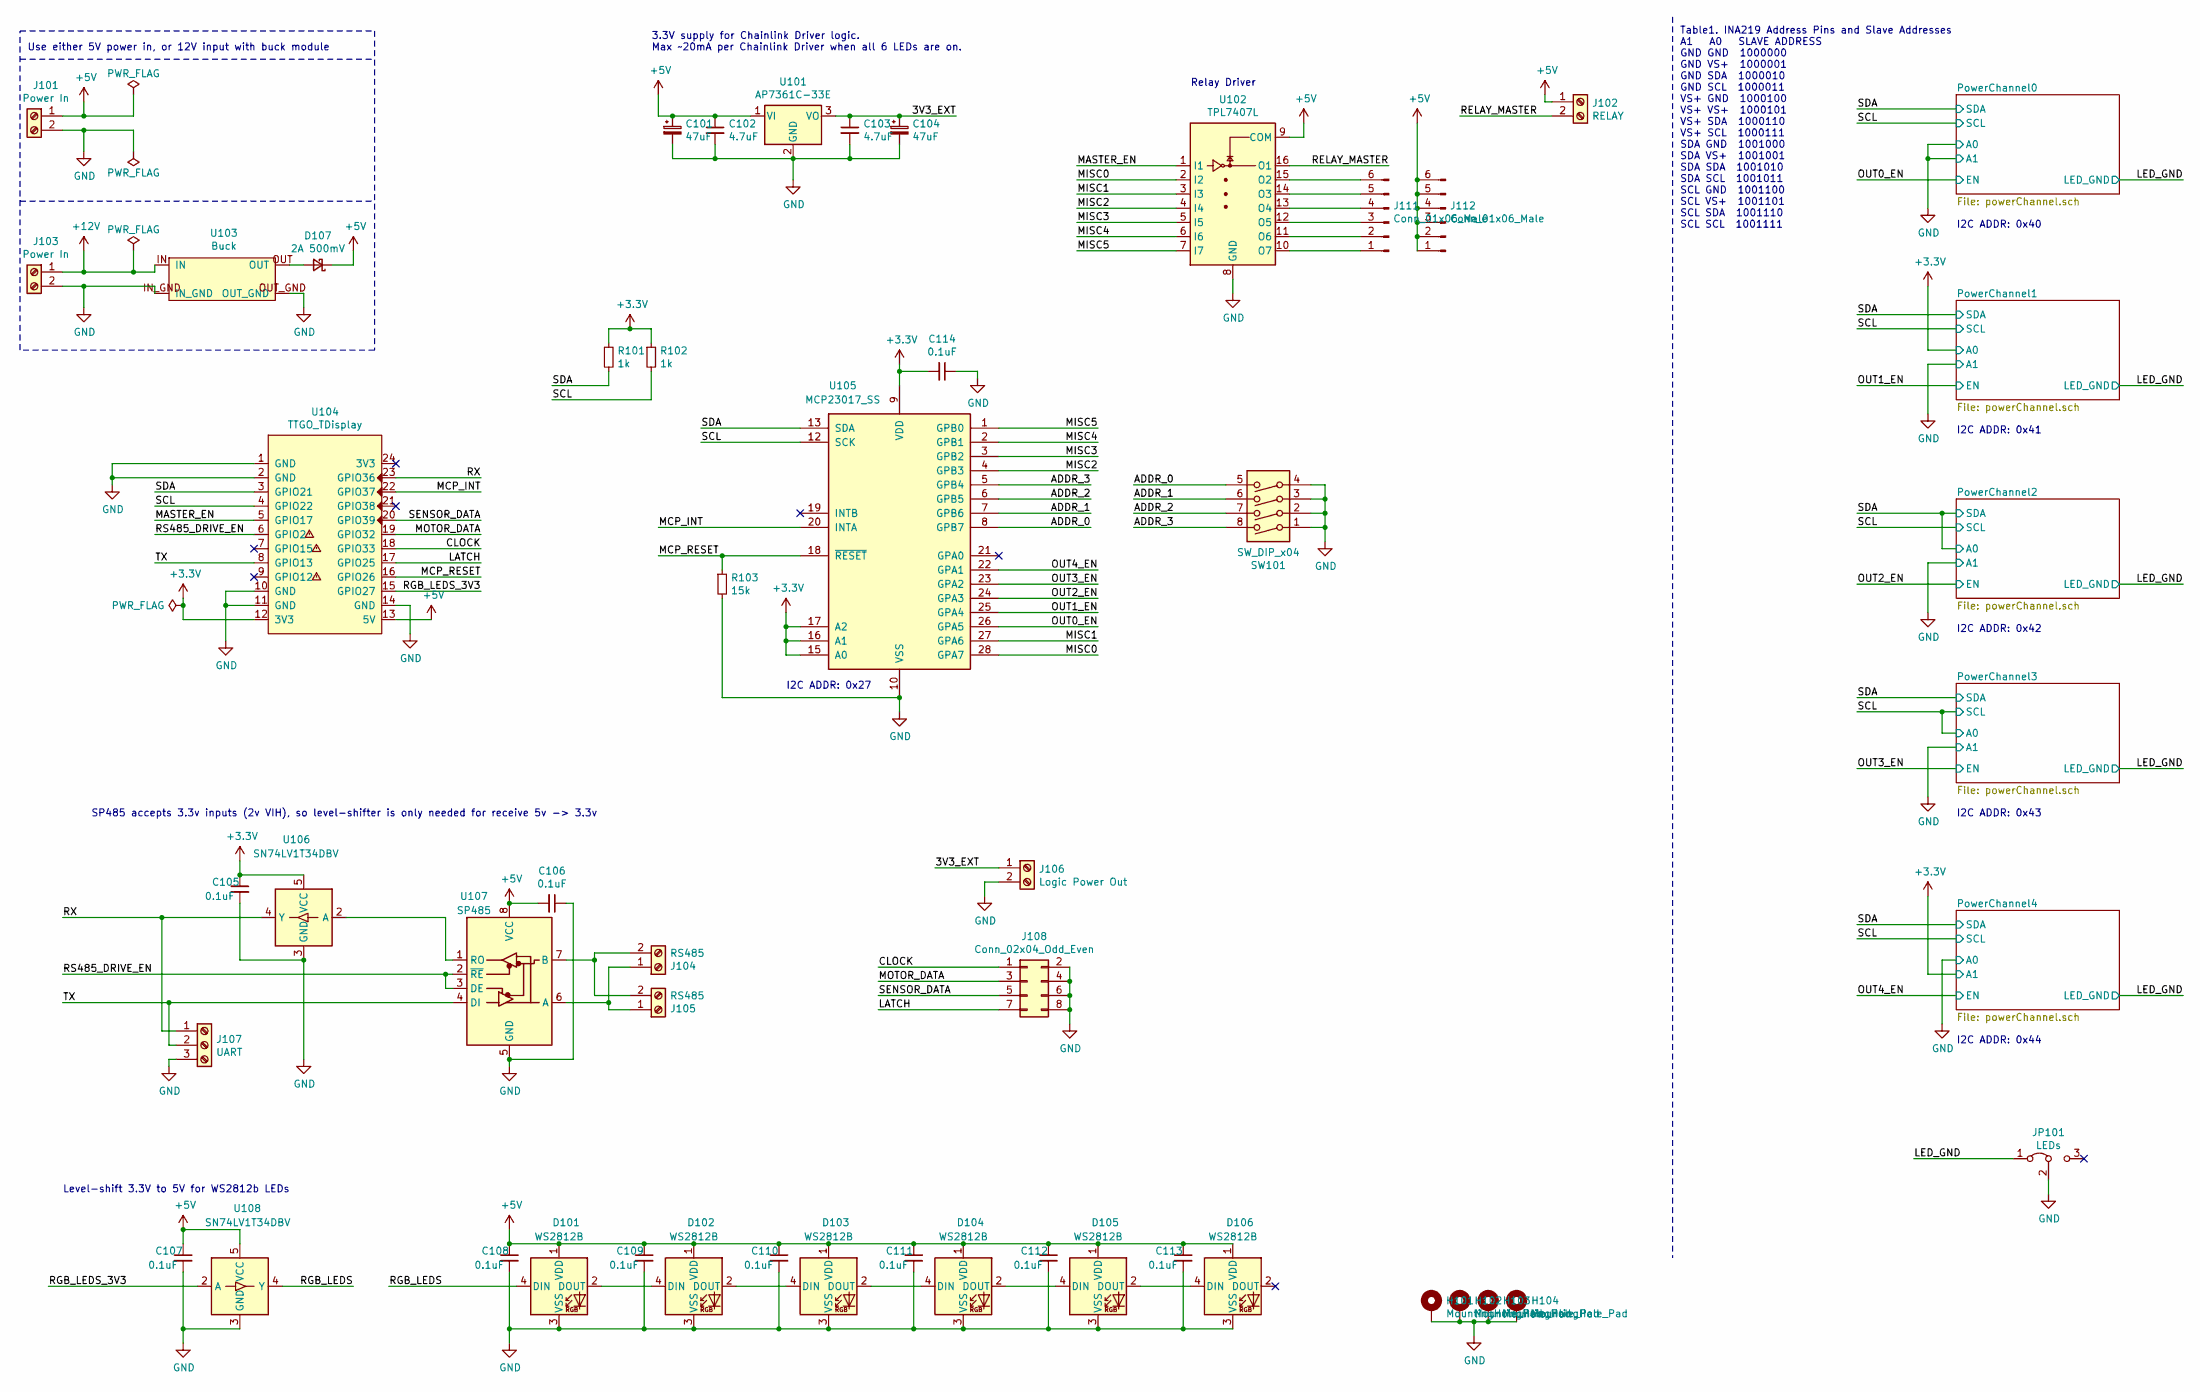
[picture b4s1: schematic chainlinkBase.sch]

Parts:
C101, C104: 47uF; CP_Elec_6.3x5.4
C102, C103: 4.7uF; C_0805_2012Metric
C105, C106, C107, C108, C109, C110, C111, C112, C113, C114: 0.1uF; C_0805_2012Metric
D101, D102, D103, D104, D105, D106: WS2812B; LED_WS2812B_PLCC4_5.0x5.0mm_P3.2mm
D107: 2A 500mV; D_SOD-128
H101, H102, H103, H104: MountingHole_Pad; MountingHole_3.2mm_M3_ISO7380_Pad
J101, J103: Power In; Generic-5.08-2P
J102: RELAY; Generic-5.08-2P
J104, J105: RS485; Generic-5.08-2P
J106: Logic Power Out; Generic-5.08-2P
J107: UART; Generic-5.08-3P
J108: Conn_02x04_Odd_Even; IDC-Header_2x04_P2.54mm_Vertical
J111, J112: Conn_01x06_Male; PinHeader_1x06_P2.54mm_Vertical
JP101: LEDs; PinHeader_1x03_P2.54mm_Vertical_SolderJumper
R101, R102: 1k; R_0805_2012Metric
R103: 15k; R_0805_2012Metric
SW101: SW_DIP_x04; SW_DIP_SPSTx04_Slide_Omron_A6S-410x_W8.9mm_P2.54mm
U101: AP7361C-33E; SOT-223-3_TabPin2
U102: TPL7407L; SOIC-16_3.9x9.9mm_P1.27mm_silk
U103: Buck; BuckModuleBackSilk
U104: TTGO_TDisplay; T-DISPLAY_extra_pins_labeled
U105: MCP23017_SS; SSOP-28_5.3x10.2mm_P0.65mm
U106, U108: SN74LV1T34DBV; SOT-23-5
U107: SP485; SOIC-8_3.9x4.9mm_P1.27mm

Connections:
+3V3: C105.1, C114.2, R101.1, R102.1, U104.12 (3V3), U105.9 (VDD), U105.15 (A0), U105.16 (A1), U105.17 (A2), U106.5 (VCC); also elsewhere on the board
+5V: C101.1, C102.1, C106.2, C107.1, C108.1, C109.1, C110.1, C111.1, C112.1, C113.1, D101.1 (VDD), D102.1 (VDD), D103.1 (VDD), D104.1 (VDD), D105.1 (VDD), D106.1 (VDD), D107.1 (K), J101.1, J102.1, J112.1, J112.2, J112.3, J112.4, J112.5, J112.6, U101.1 (VI), U102.9 (COM), U104.13 (5V), U107.8 (VCC), U108.5 (VCC)
+12V: J103.1, U103.IN
/3V3_EXT: C103.1, C104.1, J106.1, U101.3 (VO)
/ADDR_0: SW101.5, U105.8 (GPB7)
/ADDR_1: SW101.6, U105.7 (GPB6)
/ADDR_2: SW101.7, U105.6 (GPB5)
/ADDR_3: SW101.8, U105.5 (GPB4)
/CLOCK: J108.1, U104.18 (GPIO33)
/LATCH: J108.7, U104.17 (GPIO25)
/LED_GND: JP101.1 (A); also elsewhere on the board
/MASTER_EN: U102.1 (I1), U104.5 (GPIO17)
/MCP_INT: U104.22 (GPIO37), U105.20 (INTA)
/MCP_RESET: R103.1, U104.16 (GPIO26), U105.18 (~RESET~)
/MISC0: U102.2 (I2), U105.28 (GPA7)
/MISC1: U102.3 (I3), U105.27 (GPA6)
/MISC2: U102.4 (I4), U105.4 (GPB3)
/MISC3: U102.5 (I5), U105.3 (GPB2)
/MISC4: U102.6 (I6), U105.2 (GPB1)
/MISC5: U102.7 (I7), U105.1 (GPB0)
/MOTOR_DATA: J108.3, U104.19 (GPIO32)
/OUT0_EN: U105.26 (GPA5); also elsewhere on the board
/OUT1_EN: U105.25 (GPA4); also elsewhere on the board
/OUT2_EN: U105.24 (GPA3); also elsewhere on the board
/OUT3_EN: U105.23 (GPA2); also elsewhere on the board
/OUT4_EN: U105.22 (GPA1); also elsewhere on the board
/RELAY_MASTER: J102.2, U102.16 (O1)
/RGB_LEDS: D101.4 (DIN), U108.4 (Y)
/RGB_LEDS_3V3: U104.15 (GPIO27), U108.2 (A)
/RS485_DRIVE_EN: U104.6 (GPIO2), U107.2 (~RE), U107.3 (DE)
/RX: J107.1, U104.23 (GPIO36), U106.4 (Y)
/SCL: R102.2, U104.4 (GPIO22), U105.12 (SCK); also elsewhere on the board
/SDA: R101.2, U104.3 (GPIO21), U105.13 (SDA); also elsewhere on the board
/SENSOR_DATA: J108.5, U104.20 (GPIO39)
/TX: J107.2, U104.8 (GPIO13), U107.4 (DI)
GND: C101.2, C102.2, C103.2, C104.2, C105.2, C106.1, C107.2, C108.2, C109.2, C110.2, C111.2, C112.2, C113.2, C114.1, D101.3 (VSS), D102.3 (VSS), D103.3 (VSS), D104.3 (VSS), D105.3 (VSS), D106.3 (VSS), H101.1, H102.1, H103.1, H104.1, J101.2, J103.2, J106.2, J107.3, J108.2, J108.4, J108.6, J108.8, JP101.2 (C), R103.2, SW101.1, SW101.2, SW101.3, SW101.4, U101.2 (GND), U102.8 (GND), U103.IN_GND, U103.OUT_GND, U104.1 (GND), U104.2 (GND), U104.10 (GND), U104.11 (GND), U104.14 (GND), U105.10 (VSS), U106.3 (GND), U107.5 (GND), U108.3 (GND); also elsewhere on the board
unnamed: D101.2 (DOUT), D102.4 (DIN)
unnamed: D102.2 (DOUT), D103.4 (DIN)
unnamed: D103.2 (DOUT), D104.4 (DIN)
unnamed: D104.2 (DOUT), D105.4 (DIN)
unnamed: D105.2 (DOUT), D106.4 (DIN)
unnamed: D107.2 (A), U103.OUT
unnamed: J104.1, J105.1, U107.6 (A)
unnamed: J104.2, J105.2, U107.7 (B)
unnamed: J111.1, U102.10 (O7)
unnamed: J111.2, U102.11 (O6)
unnamed: J111.3, U102.12 (O5)
unnamed: J111.4, U102.13 (O4)
unnamed: J111.5, U102.14 (O3)
unnamed: J111.6, U102.15 (O2)
unnamed: U106.2 (A), U107.1 (RO)

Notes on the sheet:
Relay Driver
I2C ADDR: 0x27
I2C ADDR: 0x40
Level-shift 3.3V to 5V for WS2812b LEDs
SP485 accepts 3.3v inputs (2v VIH), so level-shifter is only needed for receive 5v -> 3.3v
3.3V supply for Chainlink Driver logic. Max ~~20mA per Chainlink Driver when all 6 LEDs are on.
Use either 5V power in, or 12V input with buck module
Table1. INA219 Address Pins and Slave Addresses A1 A0 SLAVE ADDRESS GND GND 1000000 GND VS+ 1000001 GND SDA 1000010 GND SCL 1000011 VS+ GND 1000100 VS+ VS+ 1000101 VS+ SDA 1000110 VS+ SCL 1000111 SDA GND 1001000 SDA VS+ 1001001 SDA SDA 1001010 SDA SCL 1001011 SCL GND 1001100 SCL VS+ 1001101 SCL SDA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
I2C ADDR: 0x41
I2C ADDR: 0x42
I2C ADDR: 0x43
I2C ADDR: 0x44

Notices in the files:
README.md:
License:
I'd love to hear your thoughts and questions about this project, and happy to incorporate any feedback you might have into these designs! Please feel free (and encouraged) to [open GitHub issues](https://github.com/scottbez1/splitflap/issues/new), email me directly, reach out [on Twitter](https://twitter.com/scottbez1), and [get involved](https://github.com/scottbez1/splitflap/pulls) in the open source development and let's keep chatting and building together!
This project is licensed under Apache v2 (see [LICENSE.txt](LICENSE.txt)).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
